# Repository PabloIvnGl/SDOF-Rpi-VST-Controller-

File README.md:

# SDOF-Rpi-VST-Controller-
MIDI class compliant controller VST host based on RaspberryPi 5 SBC.  

Este repositorio contiene todos los archivos correspondientes al proyecto "SDOF DELAY CONTROL"  
Este consiste en un procesador digital de efectos de audio pensado para trabajar junto con una
interface de audio.  
El procesador esta basado en una computadora de una sola placa modelo RasapberryPi 5 de 8Gb de memoria
y un cpu arm de 2.4ghz, para procesos digitales, un microcontrolador sparkfun promicro permite su control
y consolida una superficie MIDI class compliant USB incorpora además una pantalla táctil para su interacción
con el sistema operativo Linux. En un futuro el poyecto pretende compilar una distribución propia de Linux para ejecutar
unicamente una estacion digital de audio. Actualmente se utiliza la distribución "Debian" y el daw "Waveform traktion"

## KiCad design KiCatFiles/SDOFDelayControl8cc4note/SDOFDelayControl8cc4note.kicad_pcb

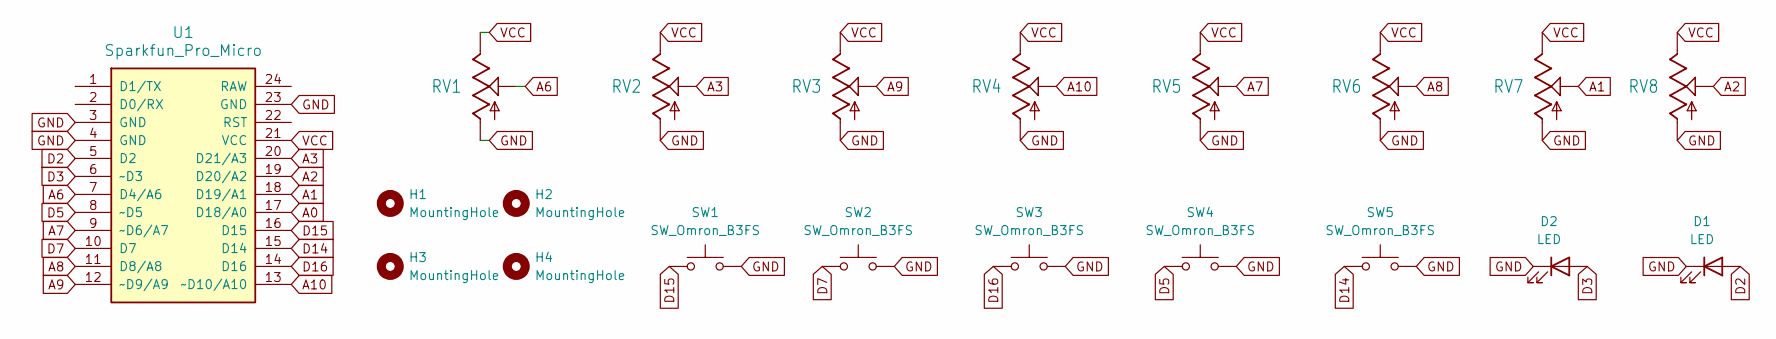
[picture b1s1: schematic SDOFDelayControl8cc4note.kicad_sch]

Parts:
D1, D2: LED; LED_D3.0mm
H1, H2, H3, H4: MountingHole; MountingHole_3mm
RV1, RV2, RV3, RV4: PotAlpsRK09RV09
RV5, RV6, RV7, RV8: B10375mmBehringer
SW1, SW2, SW3, SW4, SW5: SW_Omron_B3FS; Omron_B3F
U1: Sparkfun_Pro_Micro

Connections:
A0: U1.17 (D18/A0)
A1: RV7.2, U1.18 (D19/A1)
A2: RV8.2, U1.19 (D20/A2)
A3: RV2.2, U1.20 (D21/A3)
A6: RV1.2, U1.7 (D4/A6)
A7: RV5.2, U1.9 (~D6/A7)
A8: RV6.2, U1.11 (D8/A8)
A9: RV3.2, U1.12 (~D9/A9)
A10: RV4.2, U1.13 (~D10/A10)
D2: D1.2 (A), U1.5 (D2)
D3: D2.2 (A), U1.6 (~D3)
D5: SW4.1, U1.8 (~D5)
D7: SW2.1, U1.10 (D7)
D14: SW5.1, U1.15 (D14)
D15: SW1.1, U1.16 (D15)
D16: SW3.1, U1.14 (D16)
GND: D1.1 (K), D2.1 (K), RV1.1, RV2.1, RV3.1, RV4.1, RV5.1, RV6.1, RV7.1, RV8.1, SW1.2, SW2.2, SW3.2, SW4.2, SW5.2, U1.3 (GND), U1.4 (GND), U1.23 (GND)
VCC: RV1.3, RV2.3, RV3.3, RV4.3, RV5.3, RV6.3, RV7.3, RV8.3, U1.21 (VCC)

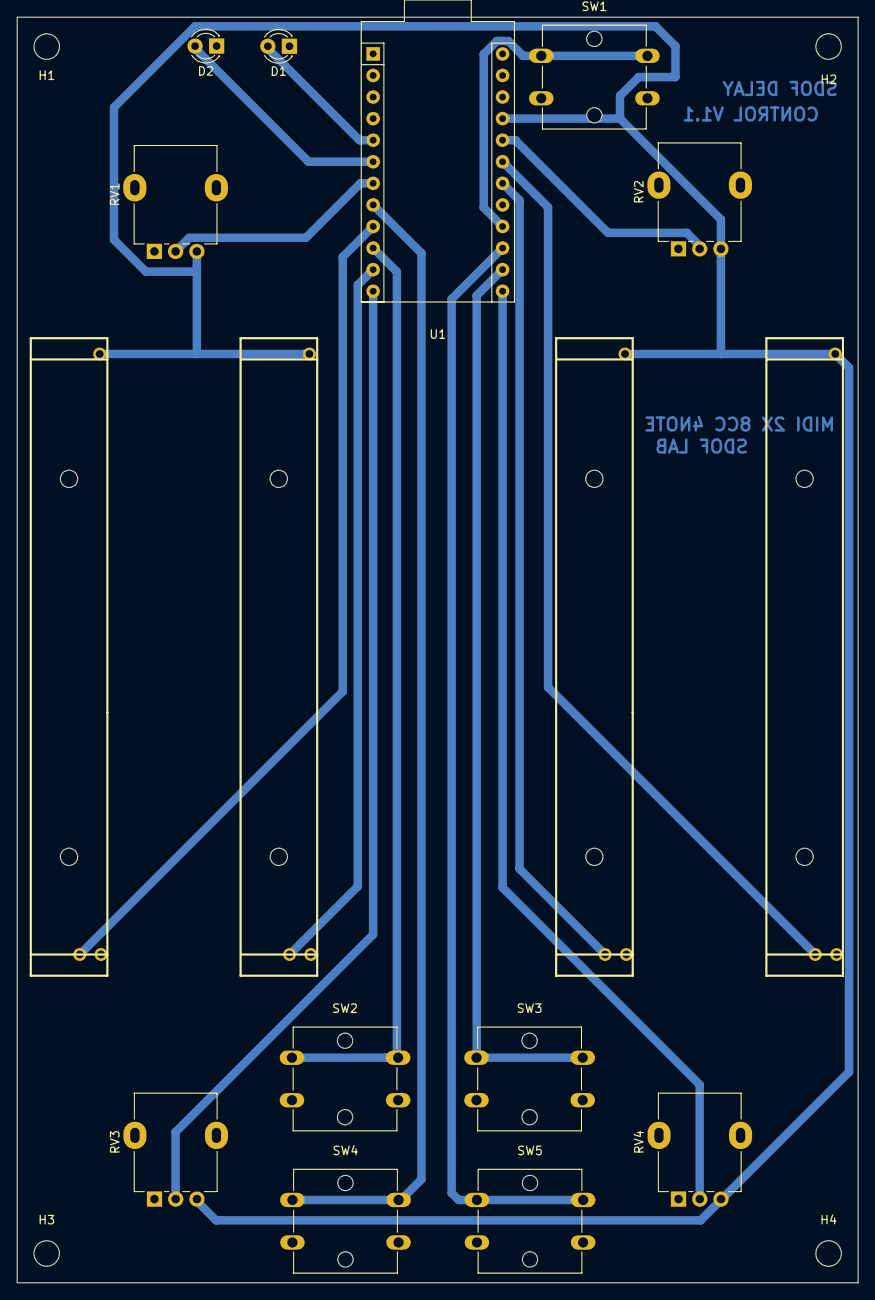
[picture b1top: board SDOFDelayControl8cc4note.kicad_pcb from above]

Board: 2 copper layers, 99.0 x 149.0 mm, 20 parts (0 on the bottom side), 17 nets.

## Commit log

2026-03-04 Add MIDIUSB submodule to project
2026-03-04 Fix MIDIUSB submodule URL format
2026-03-04 Update and rename IDE-Arduino/Dependencias/MIDIUSB.h to IDE-Arduino/Dependencias/MIDIUSB/midiusbclon
2026-03-04 Create
2026-03-04 Create r
